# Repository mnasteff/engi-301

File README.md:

# engi-301
301 PCB Eagle Project

# This project is creating Eagle libraries for different components

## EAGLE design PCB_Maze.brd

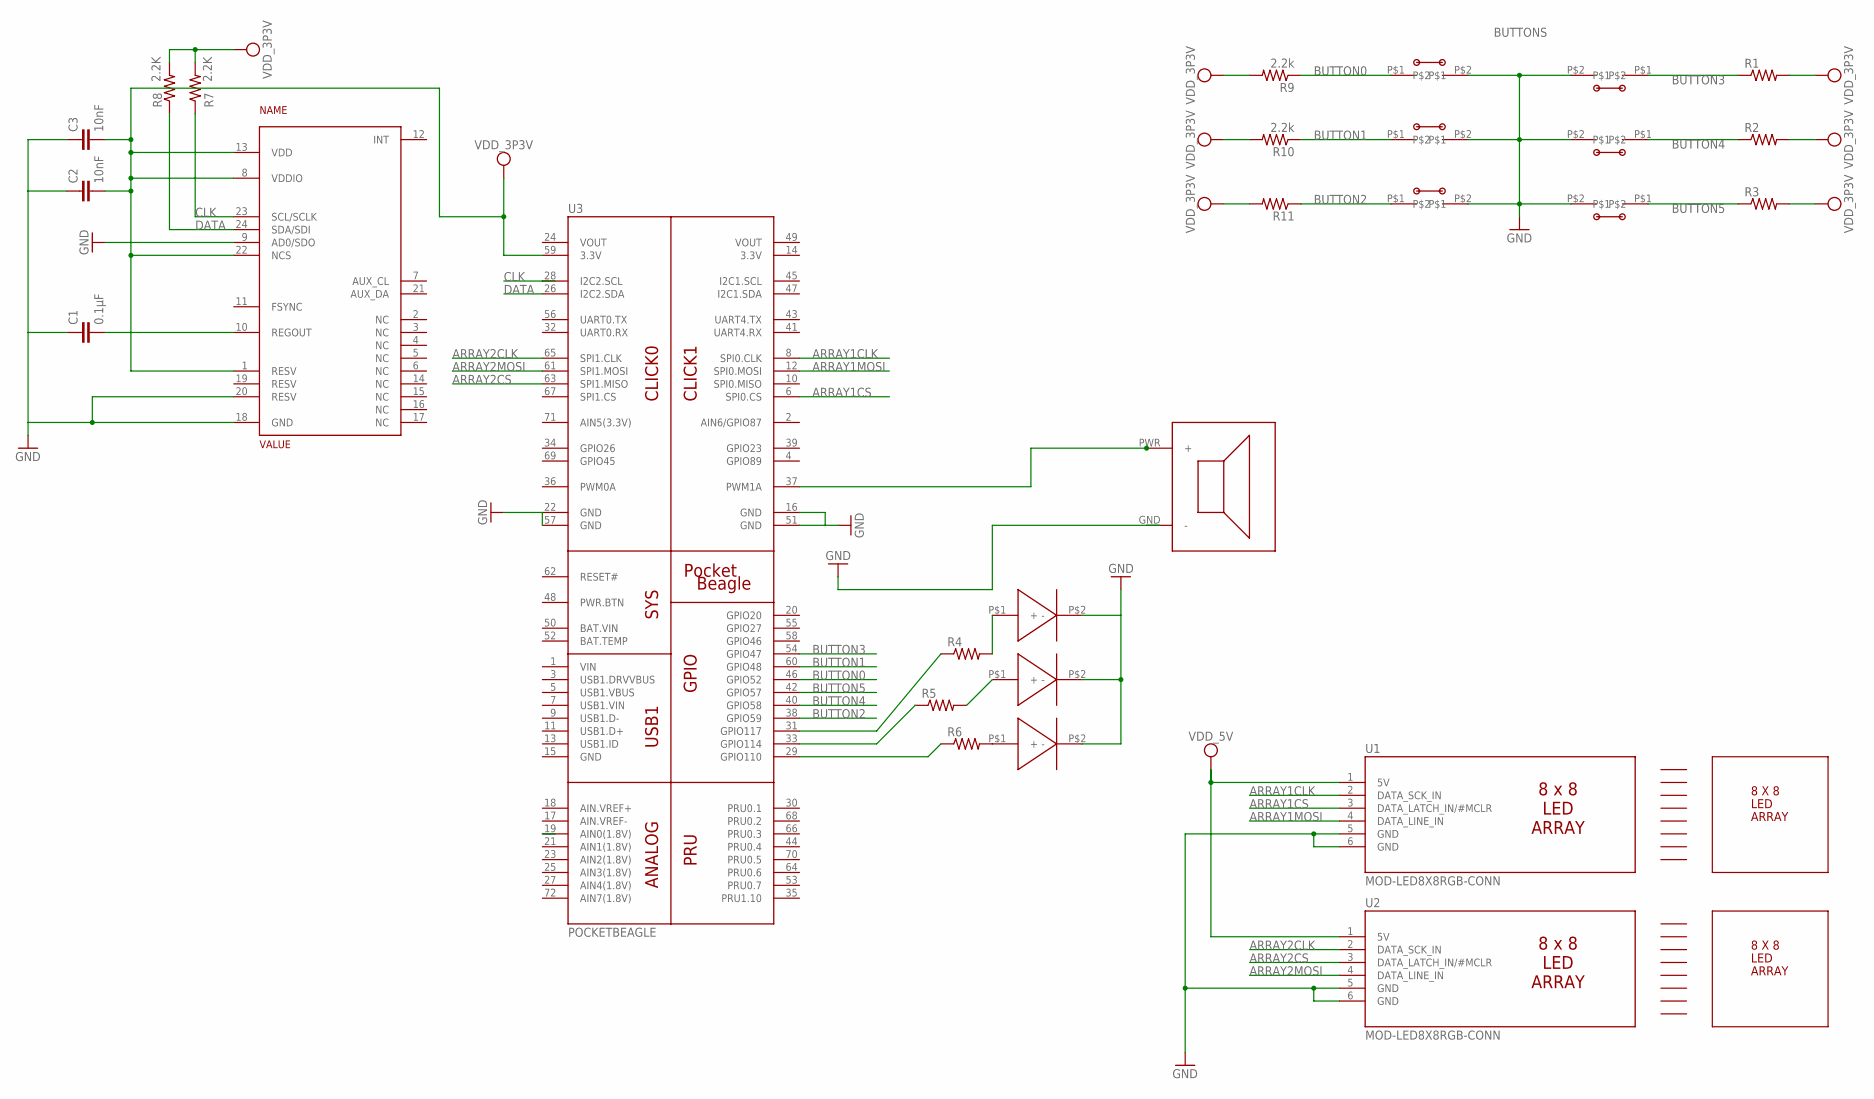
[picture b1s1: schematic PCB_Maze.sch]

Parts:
C1: 0.1µF; C0402
C2, C3: 10nF; C0402
R1, R2, R3, R4, R5, R6, R11: R_R0402; R0402
R7, R8: 2.2K; R0402
R9, R10: 2.2k; R0402
U1, U2: MOD-LED8X8RGB-CONN; FE06W
U3: POCKETBEAGLE
U$1, U$2, U$3, U$5, U$6, U$13: BUTTON; SC203
U$8, U$9, U$10: LED; C191TBKT
U$11: BUZZER; CEM-1203
U$12: MPU9250; QFN_3MMX3MM

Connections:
ARRAY1CLK: U1.2 (DATA_SCK_IN), U3.8 (SPI0.CLK)
ARRAY1CS: U1.3 (DATA_LATCH_IN/#MCLR), U3.6 (SPI0.CS)
ARRAY1MOSI: U1.4 (DATA_LINE_IN), U3.12 (SPI0.MOSI)
ARRAY2CLK: U2.2 (DATA_SCK_IN), U3.65 (SPI1.CLK)
ARRAY2CS: U2.3 (DATA_LATCH_IN/#MCLR), U3.63 (SPI1.MISO)
ARRAY2MOSI: U2.4 (DATA_LINE_IN), U3.61 (SPI1.MOSI)
BUTTON0: R9.1, U3.46 (GPIO52), U$5.P$1
BUTTON1: R10.1, U3.60 (GPIO48), U$6.P$1
BUTTON2: R11.1, U3.38 (GPIO59), U$13.P$1
BUTTON3: R1.1, U3.54 (GPIO47), U$1.P$1
BUTTON4: R2.1, U3.40 (GPIO58), U$2.P$1
BUTTON5: R3.1, U3.42 (GPIO57), U$3.P$1
CLK: R7.1, U3.28 (I2C2.SCL), U$12.23 (SCL/SCLK)
DATA: R8.1, U3.26 (I2C2.SDA), U$12.24 (SDA/SDI)
GND: C1.1, C2.1, C3.1, U1.5 (GND), U1.6 (GND), U2.5 (GND), U2.6 (GND), U3.16 (GND), U3.22 (GND), U3.51 (GND), U3.57 (GND), U$1.P$2, U$2.P$2, U$3.P$2, U$5.P$2, U$6.P$2, U$8.P$2 (-), U$9.P$2 (-), U$10.P$2 (-), U$12.9 (AD0/SDO), U$12.18 (GND), U$12.20 (RESV), U$13.P$2
unnamed: C1.2, U$12.10 (REGOUT)
unnamed: R6.1, U3.29 (GPIO110)
unnamed: R6.2, U$10.P$1 (+)
unnamed: R5.1, U3.33 (GPIO114)
unnamed: U3.37 (PWM1A), U$11.PWR (+)
unnamed: R5.2, U$9.P$1 (+)
unnamed: R4.2, U$8.P$1 (+)
unnamed: R4.1, U3.31 (GPIO117)
SYS_VDD1_3P3V: C2.2, C3.2, R1.2, R2.2, R3.2, R7.2, R8.2, R9.2, R10.2, R11.2, U3.59 (3.3V), U$12.1 (RESV), U$12.8 (VDDIO), U$12.13 (VDD), U$12.22 (NCS)
SYS_VDD1_5V: U1.1 (5V), U2.1 (5V)

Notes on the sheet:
BUTTONS
8 X 8
LED
ARRAY

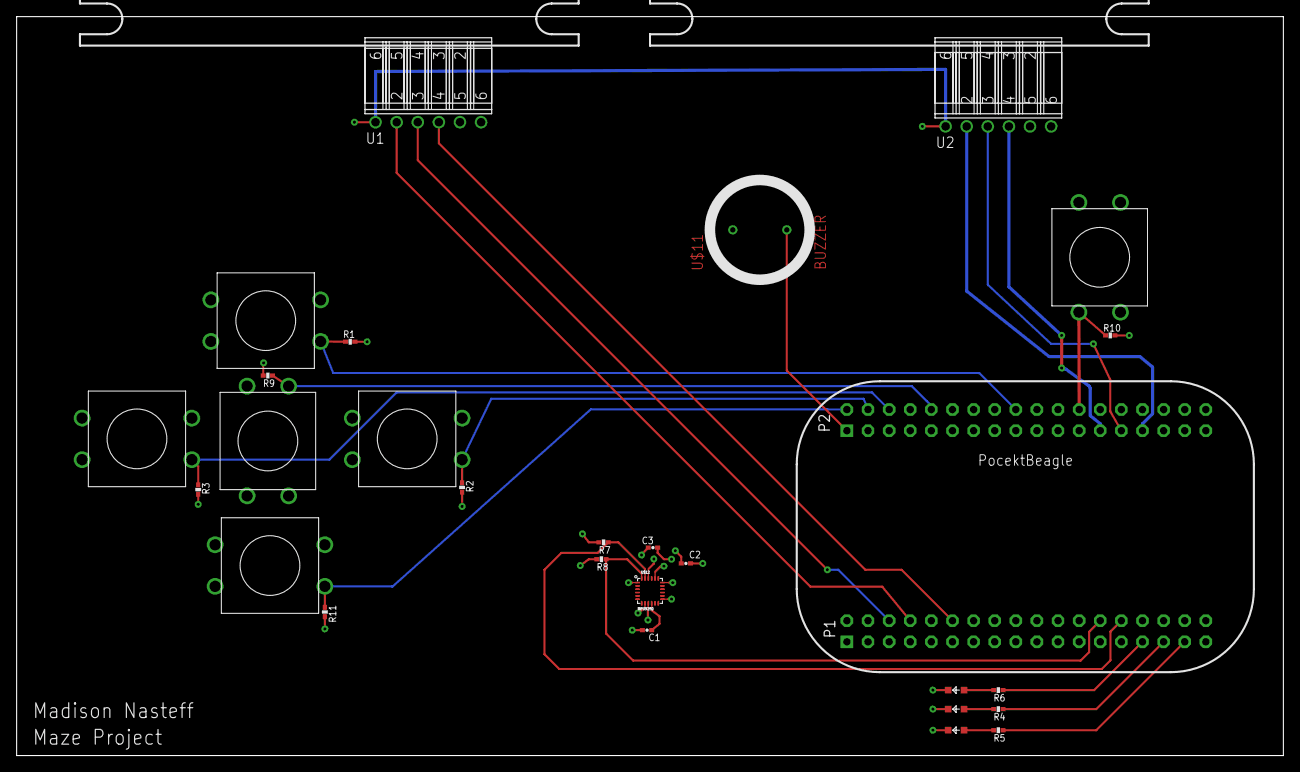
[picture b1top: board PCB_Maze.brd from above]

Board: 4 copper layers, 152.4 x 88.9 mm, 32 parts (0 on the bottom side), 25 nets.

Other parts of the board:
U$4, U$7, U$14, U$15: MOD-LED8X8RGB
